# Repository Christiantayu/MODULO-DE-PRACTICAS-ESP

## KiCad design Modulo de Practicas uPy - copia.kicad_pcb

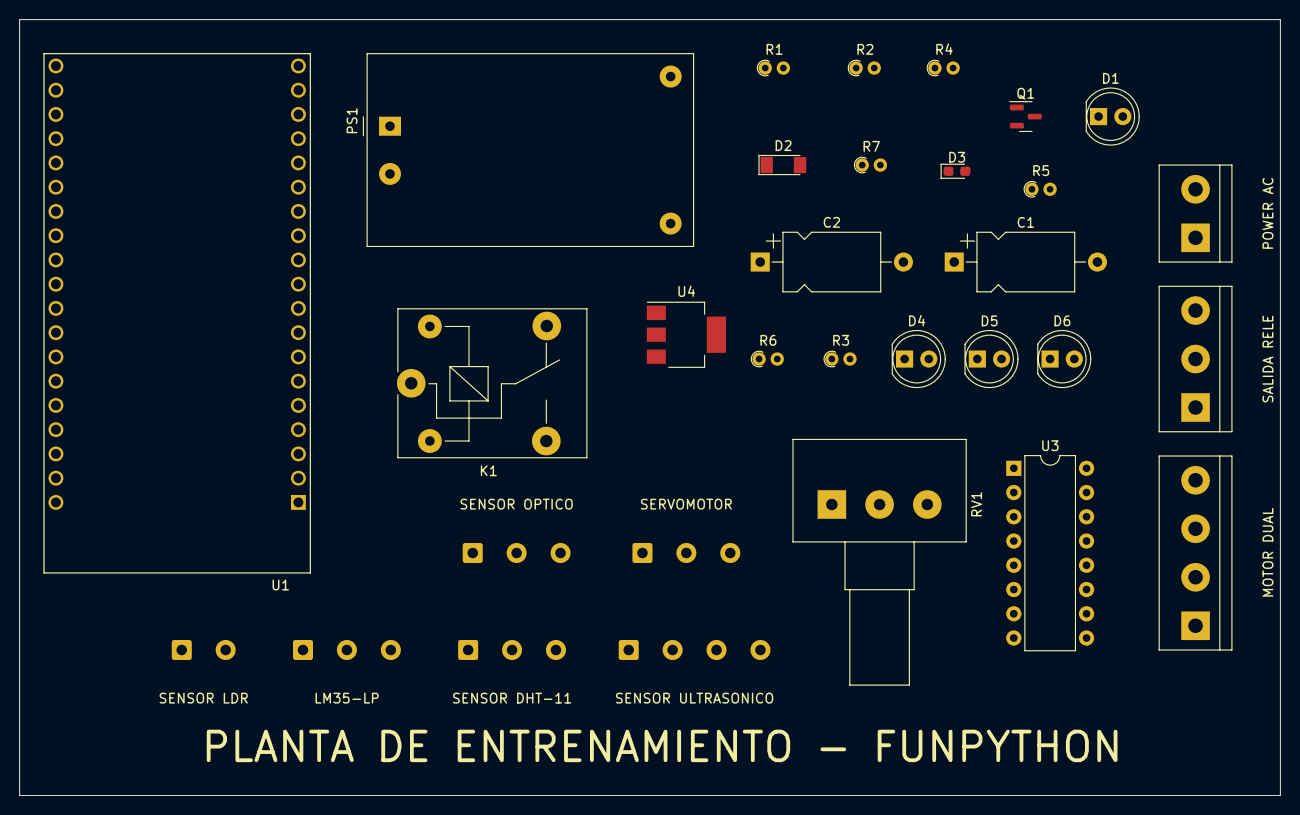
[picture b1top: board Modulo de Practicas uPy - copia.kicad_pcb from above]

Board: 2 copper layers, 132.1 x 81.3 mm, 31 parts (0 on the bottom side), 32 nets, no tracks yet.

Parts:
C1: 10uf; CP_Axial_L10.0mm_D6.0mm_P15.00mm_Horizontal
C2: 100nf; CP_Axial_L10.0mm_D6.0mm_P15.00mm_Horizontal
D1, D4, D5, D6: LED; LED_D5.0mm
D2: LL4148; D_MiniMELF
D3: LED; LED_0603_1608Metric_Pad1.05x0.95mm_HandSolder
K1: FINDER-34.51; Relay_SPDT_SANYOU_SRD_Series_Form_C
LM35-LP: LM35-LP; SolderWire-0.5sqmm_1x03_P4.6mm_D0.9mm_OD2.1mm
MOTOR DUAL: MOTOR; TerminalBlock_bornier-4_P5.08mm
POWER AC: Screw_Terminal_01x02; TerminalBlock_bornier-2_P5.08mm
PS1: HLK-PM01; Converter_ACDC_HiLink_HLK-PMxx
Q1: 2N7002; SOT-23
R1: 1k; R_Axial_DIN0204_L3.6mm_D1.6mm_P1.90mm_Vertical
R2: 2k; R_Axial_DIN0204_L3.6mm_D1.6mm_P1.90mm_Vertical
R3, R7: 10k; R_Axial_DIN0204_L3.6mm_D1.6mm_P1.90mm_Vertical
R4, R5, R6: 220ohm; R_Axial_DIN0204_L3.6mm_D1.6mm_P1.90mm_Vertical
RV1: R_Potentiometer; Potentiometer_Alps_RK163_Single_Horizontal
SALIDA RELE: SALIDA RELE; TerminalBlock_bornier-3_P5.08mm
SENSOR DHT-11: SENSOR DHT11; SolderWire-0.5sqmm_1x03_P4.6mm_D0.9mm_OD2.1mm
SENSOR LDR: SENSOR LDR; SolderWire-0.5sqmm_1x02_P4.6mm_D0.9mm_OD2.1mm
SENSOR OPTICO: SENSOR OPTICO; SolderWire-0.5sqmm_1x03_P4.6mm_D0.9mm_OD2.1mm
SENSOR ULTRASONICO: SENSOR ULTRASONICO; SolderWire-0.5sqmm_1x04_P4.6mm_D0.9mm_OD2.1mm
SERVOMOTOR: Motor_Servo; SolderWire-0.5sqmm_1x03_P4.6mm_D0.9mm_OD2.1mm
U1: ESP32-DEVKITC-32D; MODULE_ESP32-DEVKITC-32D
U3: L293D; DIP-16_W7.62mm
U4: LD1117S33TR_SOT223; SOT-223-3_TabPin2

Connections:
3.3v: C2.1, U1.1 (3V3), U4.2 (VO)
5v: C1.1, D2.1 (K), K1.2, LM35-LP.1 (+VS), PS1.4 (+Vout), R1.2, RV1.1, SENSOR DHT-11.3, SENSOR OPTICO.1, SENSOR ULTRASONICO.4, SERVOMOTOR.2 (+), U3.1 (EN1,2), U3.8 (VCC2), U3.9 (EN3,4), U3.16 (VCC1), U4.3 (VI)
+12V: K1.4, SALIDA RELE.3
-5v: C1.2, C2.2, PS1.3 (-Vout), U4.1 (GND)
AC: POWER AC.1, POWER AC.2, PS1.1 (AC/L), PS1.2 (AC/N)
GND: K1.5, LM35-LP.3 (GND), Q1.2 (S), R3.1, R4.2, R5.2, R6.2, R7.1, RV1.3, SALIDA RELE.1, SENSOR DHT-11.1, SENSOR OPTICO.2, SENSOR ULTRASONICO.1, SERVOMOTOR.3 (-), U1.14 (GND1), U3.4 (GND), U3.13 (GND)
I00: D5.2 (A), U1.33 (IO0)
I02: D4.2 (A), U1.34 (IO2)
I04: D6.2 (A), U1.32 (IO4)
IO13: RV1.2, U1.15 (IO13)
IO18: SERVOMOTOR.1 (PWM), U1.28 (IO18)
IO21: LM35-LP.2 (Vout), U1.25 (IO21)
IO25: U1.9 (IO25), U3.2 (1A)
IO26: U1.10 (IO26), U3.7 (2A)
IO27: SENSOR OPTICO.3, U1.11 (IO27)
IO32: R2.2, R3.2, SENSOR ULTRASONICO.2, U1.7 (IO32)
IO33: SENSOR ULTRASONICO.3, U1.8 (IO33)
IO34: U1.5 (IO34), U3.10 (3A)
IO35: U1.6 (IO35), U3.15 (4A)
IO36: SENSOR LDR.1, U1.3 (SENSOR_VP)
unnamed: D2.2 (A), D3.1 (K), K1.1, Q1.3 (D)
unnamed: D3.2 (A), R1.1
unnamed: D4.1 (K), R4.1
unnamed: D5.1 (K), R5.1
unnamed: D6.1 (K), R6.1
unnamed: K1.3, SALIDA RELE.2
unnamed: MOTOR DUAL.1, U3.3 (1Y)
unnamed: MOTOR DUAL.2, U3.6 (2Y)
unnamed: MOTOR DUAL.3, U3.11 (3Y)
unnamed: MOTOR DUAL.4, U3.14 (4Y)
unnamed: R7.2, SENSOR LDR.2
unnamed: Q1.1 (G), R2.1

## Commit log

2022-09-12 EPC para Upy
